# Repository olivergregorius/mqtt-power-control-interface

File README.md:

# mqtt-power-control-interface

## Introduction

Micropython project for front panel header power control using the MQTT protocol

## Hardware

This project includes a Kicad project providing schematics and a board layout for placing a Raspberry Pi Pico W on it. The microcontroller acts as a lightweight
MQTT client publishing and controlling the power state of up to 12 devices that are connected via the "Intel 9-pin header" (front panel header):

!TODO include picture of front panel header here!

The microcontroller and the devices are not directly connected, instead, they are galvanically isolated from each other by optocouplers, mitigating the risk of
damage.

The power state is determined by the state of the device's power LED pins. It is active low from the microcontroller's perspective.

The power state is controlled by shorting the device's power button pins for 500 milliseconds. That means if the device initially is powered off, it will be
powered on after the power button pins have been shortened. Powering off the machine is up to the operating system's power management, e.g. on Ubuntu if the
power button is pressed shortly (500 milliseconds are sufficient) a shutdown will be initiated, powering off the device.

Thus, each device can be controlled by two GPIO pins of the microcontroller: one for the power state check, one for the power button control.

## Software

This project is written in Micropython and can be flashed onto various microcontroller boards, e.g. the Raspberry Pi Pico W.

### Required Libraries

- umqtt.simple
- micropython_ota (see [https://github.com/olivergregorius/micropython_ota](https://github.com/olivergregorius/micropython_ota))
- micropython_loki (see [https://github.com/olivergregorius/micropython_loki](https://github.com/olivergregorius/micropython_loki))

### Required Files

The following files are required to be flashed onto the microcontroller:

- `boot.py` - Bootup script containing routines for establishing WiFi connection and installing required libraries
- `mqtt.py` - MQTT client library
- `types.py` - Utility file containing type definitions
- `utils.py` - Utility file containing utility methods
- `main.py` - Main routine
- `config.py` - Config file, see `config.template.py` as reference, the keys are self explanatory

### Message Formats

The message format is JSON.

#### Power State

The power state for each device is published to the topic defined in the config in a dedicated message for each device:

```json
{
    "deviceName": "device1",
    "state": "stopped"
}
```

The `state` attribute can take the values `stopped` and `running`.

#### Power Control

The power state for each device can be controlled by sending a dedicated message for each device to the defined topic in the config:

```json
{
    "deviceName": "device1",
    "action": "powerOn"
}
```

The `action` attribute can take the values `powerOn` and `powerOff`, whereas for now both of the actions trigger a 500 millisecond power button push, regardless
of the current state of the device.

## Disclaimer

This hardware/software is provided "as is", and you use the hardware/software at your own risk. Under no circumstances shall any author be liable for direct,
indirect, special, incidental, or consequential damages resulting from the use, misuse, or inability to use this hardware/software, even if the authors have
been advised of the possibility of such damages.

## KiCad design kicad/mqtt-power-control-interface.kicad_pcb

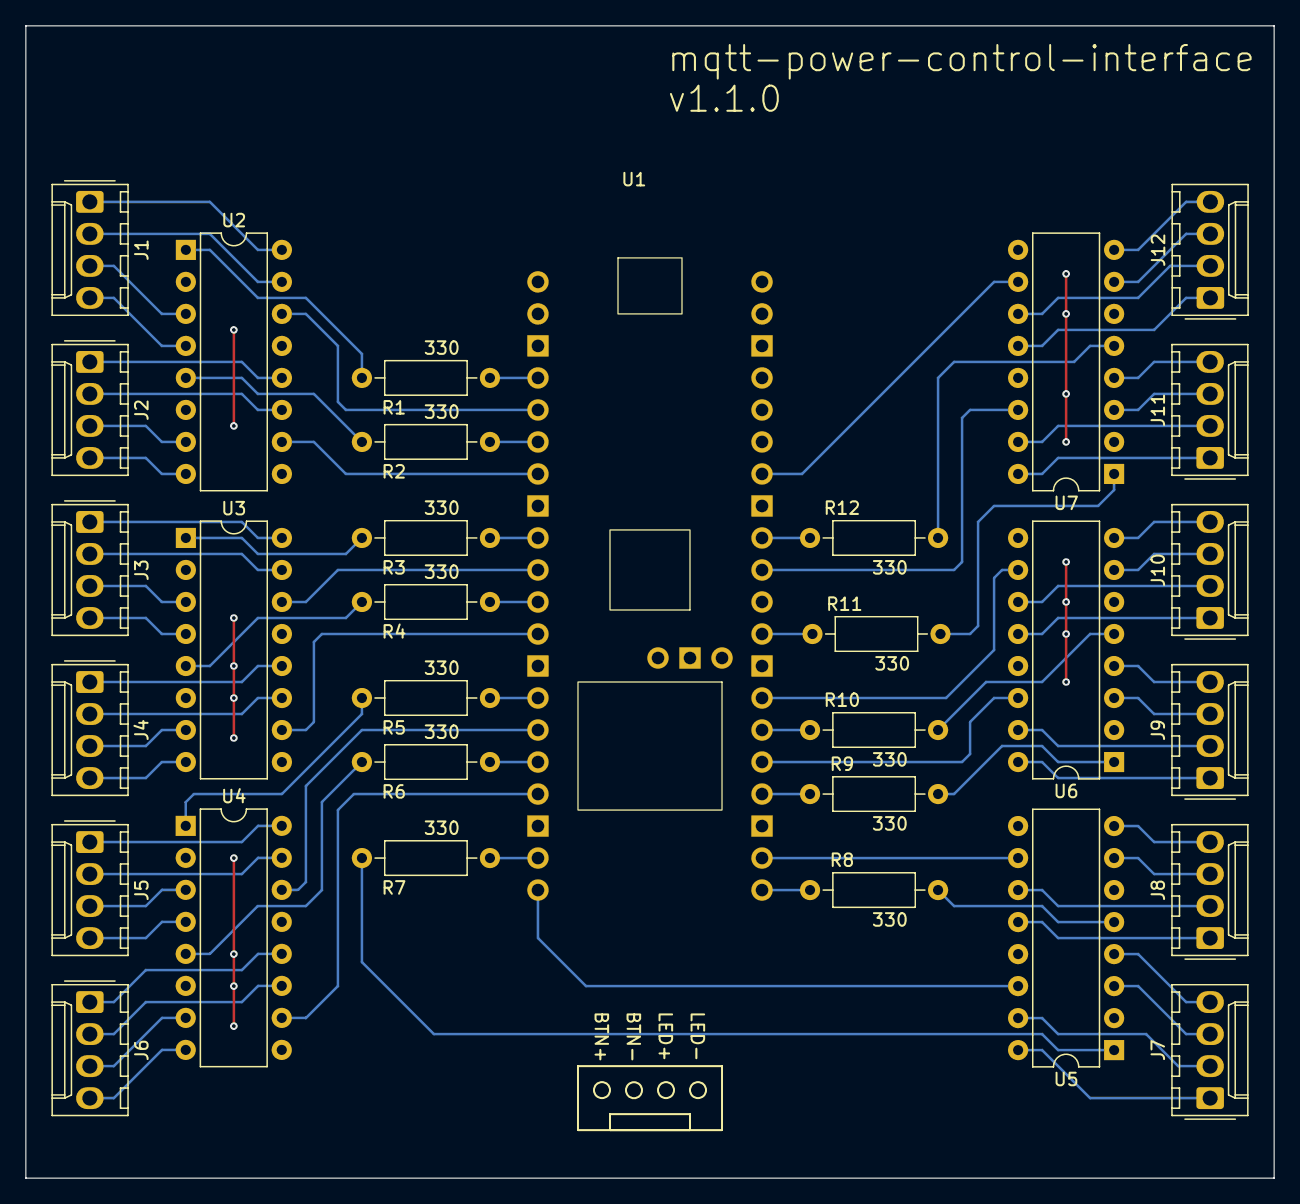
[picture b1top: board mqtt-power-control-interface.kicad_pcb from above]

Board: 2 copper layers, 99.1 x 91.4 mm, 31 parts (0 on the bottom side), 85 nets.

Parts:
J1, J2, J3, J4, J5, J6, J7, J8, J9, J10, J11, J12: Conn_01x04_Pin; Molex_KK-254_AE-6410-04A_1x04_P2.54mm_Vertical
R1, R2, R3, R4, R5, R6, R7, R8, R9, R10, R11, R12: 330; R_Axial_DIN0207_L6.3mm_D2.5mm_P10.16mm_Horizontal
U1: RPi Pico W; RPI Pico W
U2, U3, U4, U5, U6, U7: LTV-847; DIP-16_W7.62mm

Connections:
DEV1_LED+: J1.3, U2.3
DEV1_LED-: J1.4, U2.4
DEV1_SW+: J1.1, U2.16
DEV1_SW-: J1.2, U2.15
DEV2_LED+: J2.3, U2.7
DEV2_LED-: J2.4, U2.8
DEV2_SW+: J2.1, U2.12
DEV2_SW-: J2.2, U2.11
DEV3_LED+: J3.3, U3.3
DEV3_LED-: J3.4, U3.4
DEV3_SW+: J3.1, U3.16
DEV3_SW-: J3.2, U3.15
DEV4_LED+: J4.3, U3.7
DEV4_LED-: J4.4, U3.8
DEV4_SW+: J4.1, U3.12
DEV4_SW-: J4.2, U3.11
DEV5_LED+: J5.3, U4.3
DEV5_LED-: J5.4, U4.4
DEV5_SW+: J5.1, U4.16
DEV5_SW-: J5.2, U4.15
DEV6_LED+: J6.3, U4.7
DEV6_LED-: J6.4, U4.8
DEV6_SW+: J6.1, U4.12
DEV6_SW-: J6.2, U4.11
DEV7_LED+: J7.3, U5.3
DEV7_LED-: J7.4, U5.4
DEV7_SW+: J7.1, U5.16
DEV7_SW-: J7.2, U5.15
DEV8_LED+: J8.3, U5.7
DEV8_LED-: J8.4, U5.8
DEV8_SW+: J8.1, U5.12
DEV8_SW-: J8.2, U5.11
DEV9_LED+: J9.3, U6.3
DEV9_LED-: J9.4, U6.4
DEV9_SW+: J9.1, U6.16
DEV9_SW-: J9.2, U6.15
DEV10_LED+: J10.3, U6.7
DEV10_LED-: J10.4, U6.8
DEV10_SW+: J10.1, U6.12
DEV10_SW-: J10.2, U6.11
DEV11_LED+: J11.3, U7.3
DEV11_LED-: J11.4, U7.4
DEV11_SW+: J11.1, U7.16
DEV11_SW-: J11.2, U7.15
DEV12_LED+: J12.3, U7.7
DEV12_LED-: J12.4, U7.8
DEV12_SW+: J12.1, U7.12
DEV12_SW-: J12.2, U7.11
GND: U1.3 (GND1), U1.8 (GND2), U1.13 (GND3), U1.18 (GND4), U1.23 (GND5), U1.28 (GND6), U1.33 (GND7), U1.38 (GND8), U1.42 (GND_DEBUG), U2.2, U2.6, U2.9, U2.13, U3.2, U3.6, U3.9, U3.13, U4.2, U4.6, U4.9, U4.13, U5.2, U5.6, U5.9, U5.13, U6.2, U6.6, U6.9, U6.13, U7.2, U7.6, U7.9, U7.13
GPIO2: R1.1, U1.4 (GP2)
GPIO3: U1.5 (GP3), U2.14
GPIO4: R2.1, U1.6 (GP4)
GPIO5: U1.7 (GP5), U2.10
GPIO6: R3.1, U1.9 (GP6)
GPIO7: U1.10 (GP7), U3.14
GPIO8: R4.1, U1.11 (GP8)
GPIO9: U1.12 (GP9), U3.10
GPIO10: R5.1, U1.14 (GP10)
GPIO11: U1.15 (GP11), U4.14
GPIO12: R6.1, U1.16 (GP12)
GPIO13: U1.17 (GP13), U4.10
GPIO14: R7.1, U1.19 (GP14)
GPIO15: U1.20 (GP15), U5.14
GPIO16: R8.1, U1.21 (GP16)
GPIO17: U1.22 (GP17), U5.10
GPIO18: R9.1, U1.24 (GP18)
GPIO19: U1.25 (GP19), U6.14
GPIO20: R10.1, U1.26 (GP20)
GPIO21: U1.27 (GP21), U6.10
GPIO22: R11.1, U1.29 (GP22)
GPIO26: U1.31 (GP26), U7.14
GPIO27: R12.1, U1.32 (GP27)
GPIO28: U1.34 (GP28), U7.10
unnamed: R1.2, U2.1
unnamed: R2.2, U2.5
unnamed: R3.2, U3.1
unnamed: R4.2, U3.5
unnamed: R5.2, U4.1
unnamed: R6.2, U4.5
unnamed: R7.2, U5.1
unnamed: R8.2, U5.5
unnamed: R9.2, U6.1
unnamed: R10.2, U6.5
unnamed: R11.2, U7.1
unnamed: R12.2, U7.5

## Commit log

2023-08-01 First draft of implementation
2023-08-02 Code optimizations, added first schematic and board draft
2023-08-02 Removed duplicate kicad project folder
2023-08-04 Code optimizations
2023-08-07 Fixed instability issue in mqtt client
2023-08-07 Enhanced schematic and board
2023-08-07 Removed kicad backups folder
2023-08-07 Changed status to state, updated documentation
2023-08-07 Updated documentation
2023-09-15 Code optimization, included micropython_loki and micropython_ota libraries, improved failsafeness
2023-09-15 Updated board, using THT resistors, fixed wiring
2023-09-23 Code optimization, updated documentation
2024-03-22 Configured client id for MQTT
2024-06-29 v1.0.2: Fixed reconnect behavior on issues
